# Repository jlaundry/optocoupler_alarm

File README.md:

# optocoupler_alarm

A simple circuit for connecting a powered contact (such as from a garage door) to a monitored input (on an alarm system).

Order from OSH Park: https://oshpark.com/shared_projects/fjzrOZxV

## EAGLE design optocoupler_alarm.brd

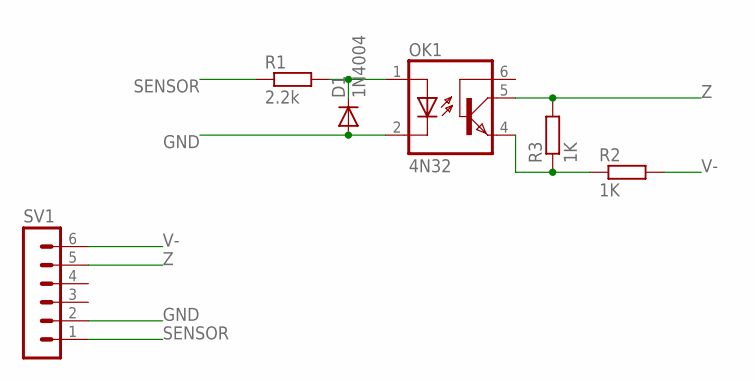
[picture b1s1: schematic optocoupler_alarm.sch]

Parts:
D1: 1N4004; DO41-10
OK1: 4N32; DIL06
R1: 2.2k; 0207/10
R2, R3: 1K; 0207/10
SV1: MA06-1

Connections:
GND: D1.A, OK1.2 (C), SV1.2
unnamed: D1.C, OK1.1 (A), R1.2
unnamed: OK1.4 (EMI), R2.1, R3.1
SENSOR: R1.1, SV1.1
V-: R2.2, SV1.6
Z: OK1.5 (COL), R3.2, SV1.5

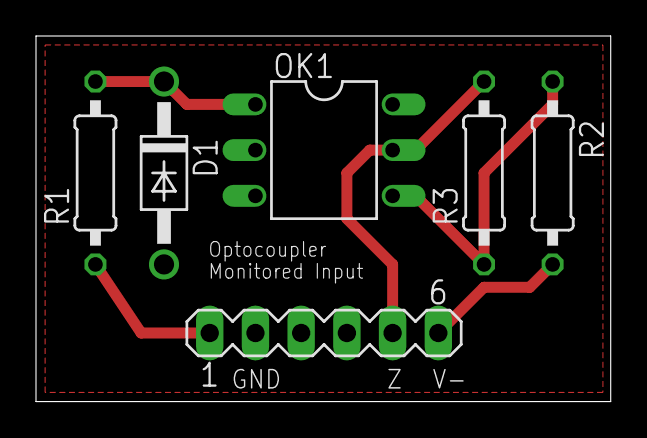
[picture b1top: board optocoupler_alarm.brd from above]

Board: 2 copper layers, 31.9 x 20.3 mm, 6 parts (0 on the bottom side), 6 nets.
